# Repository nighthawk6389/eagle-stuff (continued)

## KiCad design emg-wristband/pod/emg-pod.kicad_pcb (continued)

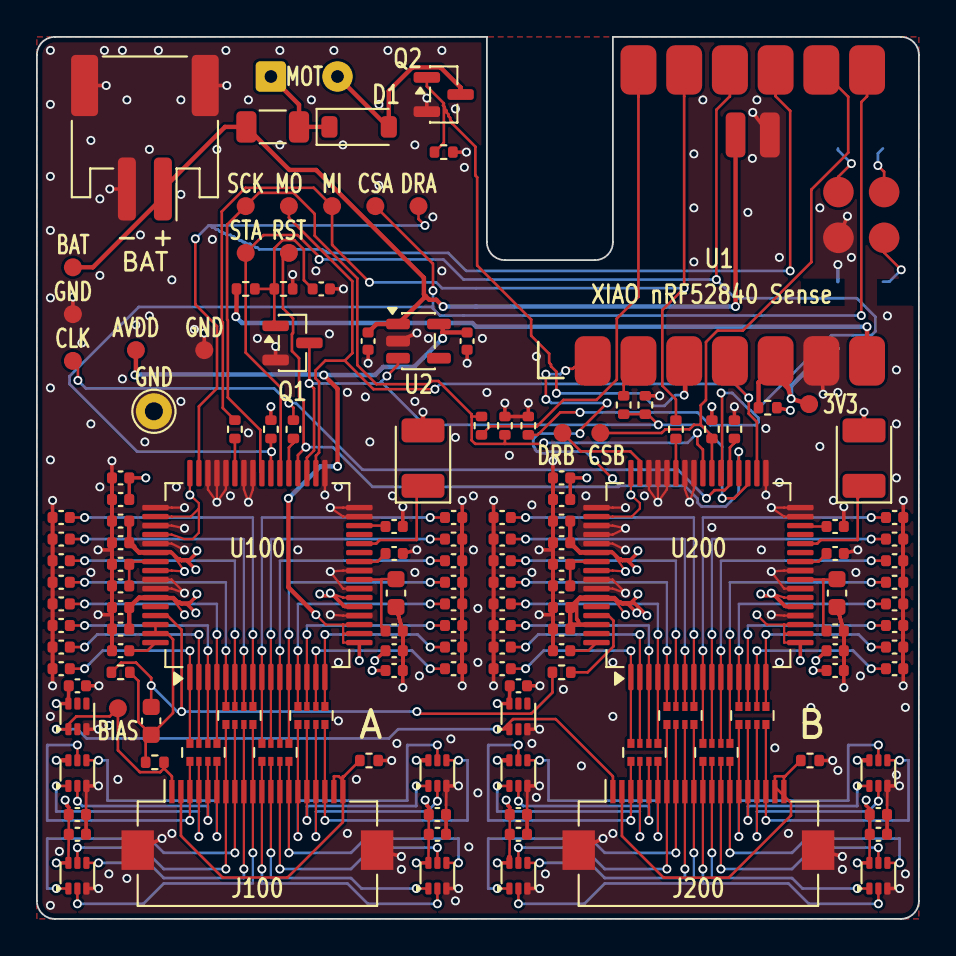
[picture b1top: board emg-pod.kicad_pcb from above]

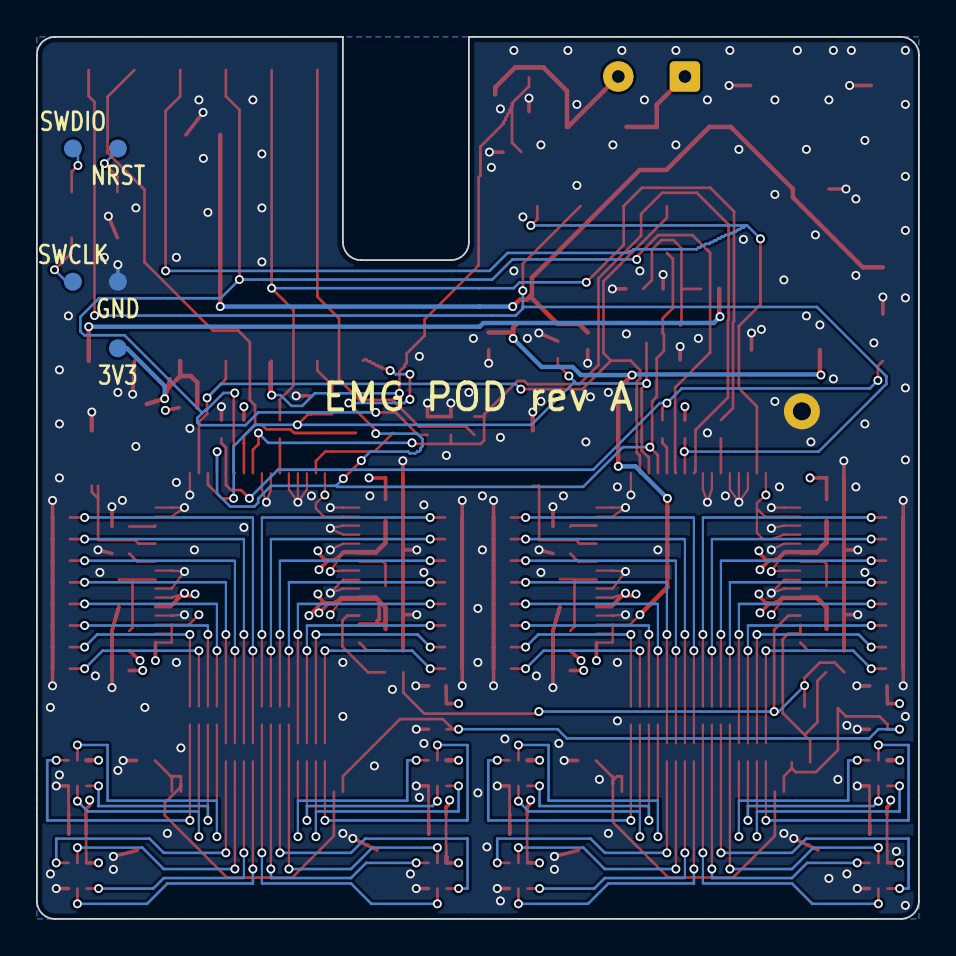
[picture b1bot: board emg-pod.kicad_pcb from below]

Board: 4 copper layers, 49.0 x 49.0 mm, 150 parts (5 on the bottom side), 111 nets.

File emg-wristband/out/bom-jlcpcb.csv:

Comment,Designator,Footprint,LCSC Part #,Manufacturer Part,Quantity
1u,"C1,C2,C120,C122,C124,C126,C131,C132,C134,C220,C222,C224,C226,C231,C232,C234",C_0402_1005Metric,C52923,CL05A105KA5NQNC,16
100n,"C3,C121,C123,C125,C127,C129,C133,C141,C142,C143,C144,C145,C221,C223,C225,C227,C229,C233,C241,C242,C243,C244,C245",C_0402_1005Metric,C1525,CL05B104KO5NNNC,23
47p,"C101,C102,C103,C104,C105,C106,C107,C108,C109,C110,C111,C112,C113,C114,C115,C116,C201,C202,C203,C204,C205,C206,C207,C208,C209,C210,C211,C212,C213,C214,C215,C216",C_0402_1005Metric,C1567,0402CG470J500NT,32
10u,"C128,C228",C_0603_1608Metric,C19702,CL10A106KP8NNNC,2
22u,"C130,C230",CP_EIA-3528-21_Kemet-B,C117031,T491B226M010AT,2
1n,"C135,C235",C_0402_1005Metric,C1523,0402B102K500NT,2
1n5,C140,C_0603_1608Metric,C1595,0603B152K500NT,1
B5819W,D1,D_SOD-123,C8598,B5819W SL,1
S2B-PH-SM4-TB,J1,JST_PH_S2B-PH-SM4-TB_1x02-1MP_P2.00mm_Horizontal,C295747,S2B-PH-SM4-TB(LF)(SN),1
FH12-20S-0.5SH,"J100,J200",Hirose_FH12-20S-0.5SH_1x20-1MP_P0.50mm_Horizontal,C596730,FH12-20S-0.5SH(55),2
AO3400A,"Q1,Q2",SOT-23,C20917,AO3400A,2
10k,"R1,R3,R4,R120,R220",R_0402_1005Metric,C25744,0402WGF1002TCE,5
100k,"R2,R6,R223",R_0402_1005Metric,C25741,0402WGF1003TCE,3
12R,R5,R_0805_2012Metric,C17445,0805W8F120JT5E,1
33R,"R20,R121,R123,R221",R_0402_1005Metric,C25105,0402WGF330JTCE,4
0R,"R122,R222,R224",R_0402_1005Metric,C17168,0402WGF0000TCE,3
1M,R124,R_0402_1005Metric,C26083,0402WGF1004TCE,1
47k,R125,R_0402_1005Metric,C25792,0402WGF4702TCE,1
47k x4,"RN101,RN102,RN103,RN104,RN201,RN202,RN203,RN204",R_Array_Convex_4x0402,C2028,4D02WGJ0473TCE,8
XIAO nRF52840 Sense,U1,XIAO-nRF52840-SMD,C17401557,Seeed 102010469,1
LP5907MFX-3.0,U2,SOT-23-5,C475492,LP5907MFX-3.0/NOPB,1
ADS1298IPAGR,"U100,U200",TQFP-64_10x10mm_P0.5mm,C527440,ADS1298IPAGR,2
TPD4E001DRL,"U101,U102,U103,U104,U105,U201,U202,U203,U204,U205",SOT-563,C527516,TPD4E001DRLR,10

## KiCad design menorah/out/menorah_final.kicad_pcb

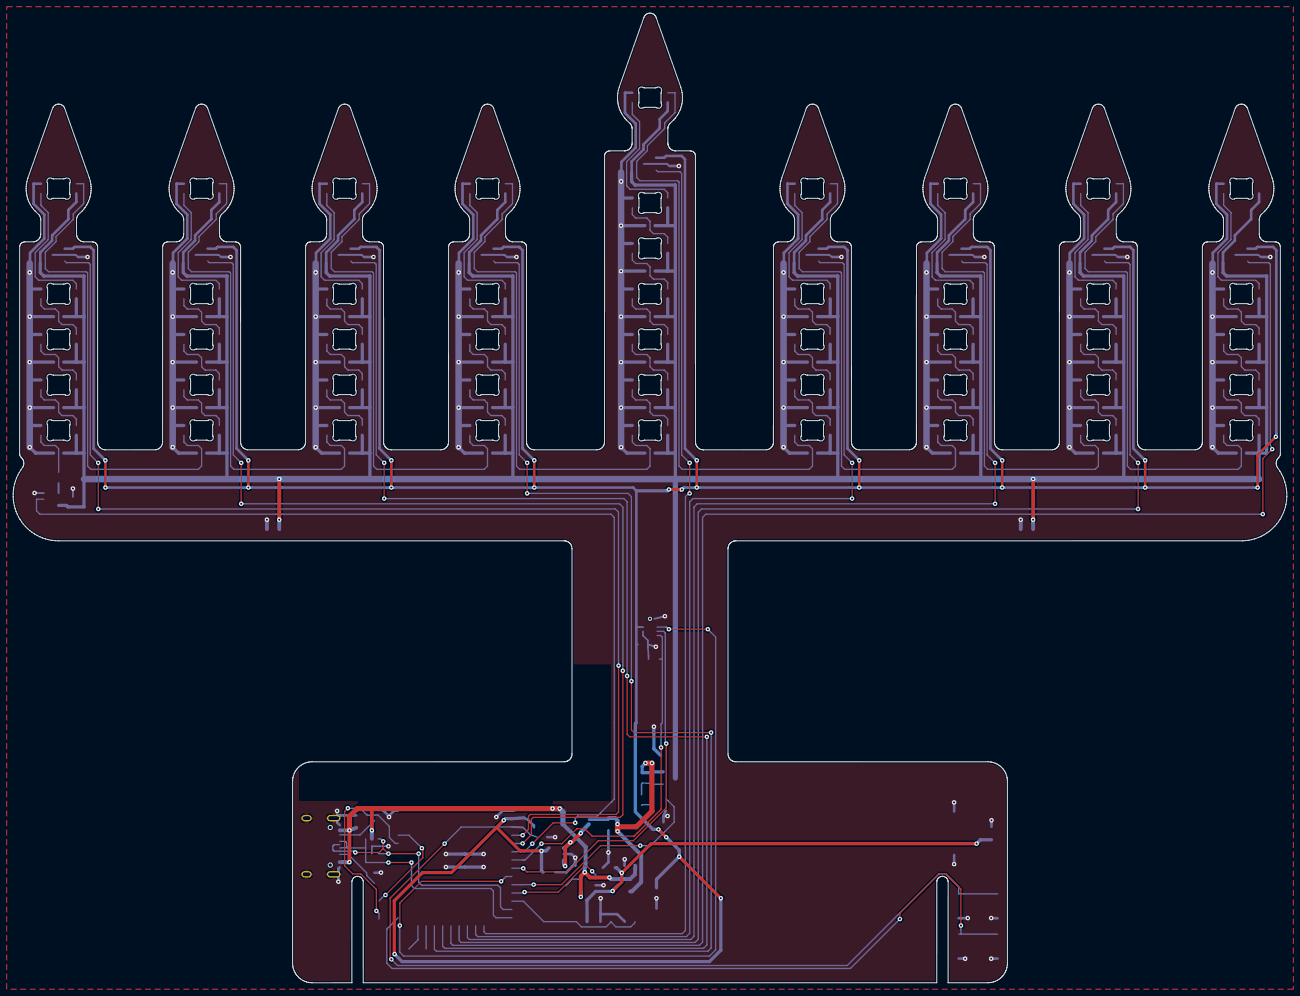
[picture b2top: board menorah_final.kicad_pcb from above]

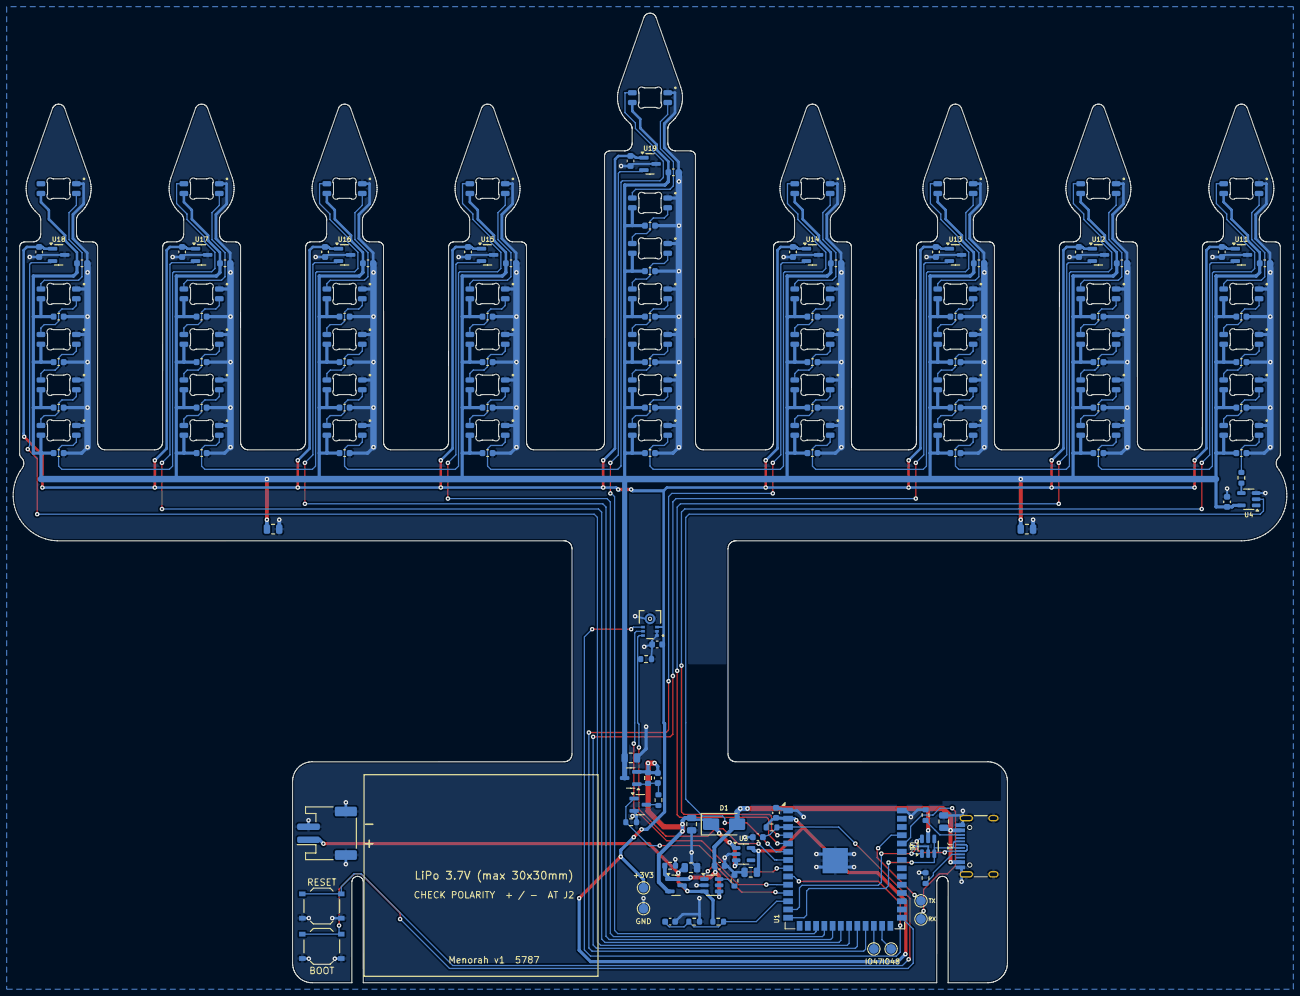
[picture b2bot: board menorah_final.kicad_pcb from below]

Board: 2 copper layers, 196.0 x 149.2 mm, 158 parts (158 on the bottom side), 83 nets.

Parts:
C1, C8, C11, C12, C101, C102, C103, C104, C105, C106, C107, C108, C109, C110, C111, C112, C113, C114, C115, C116, C117, C118, C119, C120, C121, C122, C123, C124, C125, C126, C127, C128, C129, C130, C131, C132, C133, C134, C135, C136, C137, C138, C139, C140, C141, C142, C143, C144, C145, C146, C147, C151, C152, C153, C154, C155, C156, C157, C158, C159: 100n; C_0603_1608Metric
C2, C4, C9: 1u; C_0603_1608Metric
C3, C5: 10u; C_0805_2012Metric
C6, C7, C10, C13, C14: 22u; C_0805_2012Metric
D1: SS34; D_SMA
D101, D102, D103, D104, D105, D106, D107, D108, D109, D110, D111, D112, D113, D114, D115, D116, D117, D118, D119, D120, D121, D122, D123, D124, D125, D126, D127, D128, D129, D130, D131, D132, D133, D134, D135, D136, D137, D138, D139, D140, D141, D142, D143, D144, D145, D146, D147: SK6812MINI-E; SK6812MINI-E_Rev
J1: USB-C; USB_C_Receptacle_HRO_TYPE-C-31-M-12
J2: LiPo; JST_PH_S2B-PH-SM4-TB_1x02-1MP_P2.00mm_Horizontal
MK1: ICS-43432
Q1, Q2: AO3401A; SOT-23
Q3: 2N7002; SOT-23
R1, R9: 10k; R_0603_1608Metric
R2, R3: 5k1; R_0603_1608Metric
R4: 3k3; R_0603_1608Metric
R5: 2k2; R_0603_1608Metric
R6, R7, R8, R10, R12: 100k; R_0603_1608Metric
R11: 100R; R_0603_1608Metric
SW1, SW2: TS-1187A; SW_Push_1P1T_XKB_TS-1187A
TP1: GND; TestPoint_Pad_D1.5mm
TP2: +3V3; TestPoint_Pad_D1.5mm
TP3: TX; TestPoint_Pad_D1.5mm
TP4: RX; TestPoint_Pad_D1.5mm
TP5: IO47; TestPoint_Pad_D1.5mm
TP6: IO48; TestPoint_Pad_D1.5mm
U1: ESP32-S3-WROOM-1-N8R8; ESP32-S3-WROOM-1
U2: TP4057; SOT-23-6
U3: AP2112K-3.3; SOT-23-5
U4: SN74LV1T34; SOT-23-5
U5: USBLC6-2SC6; SOT-23-6
U11, U12, U13, U14, U15, U16, U17, U18, U19: DRV5032FA; SOT-23

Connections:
+3V3: C1.1, C6.1, C12.1, C151.1, C152.1, C153.1, C154.1, C155.1, C156.1, C157.1, C158.1, C159.1, MK1.3, R1.1, TP2.1, U1.2, U3.5, U11.1, U12.1, U13.1, U14.1, U15.1, U16.1, U17.1, U18.1, U19.1
BOOT: SW1.1, U1.27
CC1: J1.A5, R3.1
CC2: J1.B5, R2.1
CHRG_N: U1.11, U2.1
EN: C2.1, R1.2, SW2.1, U1.3
EXP_IO47: TP5.1, U1.24
EXP_IO48: TP6.1, U1.25
GND: C1.2, C2.2, C3.2, C4.2, C5.2, C6.2, C7.2, C8.2, C10.2, C11.2, C12.2, C13.2, C14.2, C101.2, C102.2, C103.2, C104.2, C105.2, C106.2, C107.2, C108.2, C109.2, C110.2, C111.2, C112.2, C113.2, C114.2, C115.2, C116.2, C117.2, C118.2, C119.2, C120.2, C121.2, C122.2, C123.2, C124.2, C125.2, C126.2, C127.2, C128.2, C129.2, C130.2, C131.2, C132.2, C133.2, C134.2, C135.2, C136.2, C137.2, C138.2, C139.2, C140.2, C141.2, C142.2, C143.2, C144.2, C145.2, C146.2, C147.2, C151.2, C152.2, C153.2, C154.2, C155.2, C156.2, C157.2, C158.2, C159.2, D101.3, D102.3, D103.3, D104.3, D105.3, D106.3, D107.3, D108.3, D109.3, D110.3, D111.3, D112.3, D113.3, D114.3, D115.3, D116.3, D117.3, D118.3, D119.3, D120.3, D121.3, D122.3, D123.3, D124.3, D125.3, D126.3, D127.3, D128.3, D129.3, D130.3, D131.3, D132.3, D133.3, D134.3, D135.3, D136.3, D137.3, D138.3, D139.3, D140.3, D141.3, D142.3, D143.3, D144.3, D145.3, D146.3, D147.3, J1.A1, J1.A12, J1.B1, J1.B12, J1.S1, J2.2, J2.MP, MK1.1, MK1.2, MK1.4, Q3.2, R2.2, R3.2, R4.2, R5.2, R7.2, R10.2, R12.2, SW1.2, SW2.2, TP1.1, U1.1, U1.40, U1.41, U2.2, U3.2, U4.3, U5.2, U11.3, U12.3, U13.3, U14.3, U15.3, U16.3, U17.3, U18.3, U19.3
HALL_C1: U1.4, U11.2
HALL_C2: U1.5, U12.2
HALL_C3: U1.22, U13.2
HALL_C4: U1.23, U14.2
HALL_C5: U1.18, U15.2
HALL_C6: U1.19, U16.2
HALL_C7: U1.20, U17.2
HALL_C8: U1.21, U18.2
HALL_SH: U1.17, U19.2
LED_D0: D101.4, R11.2
LED_D1: D101.2, D102.4
LED_D2: D102.2, D103.4
LED_D3: D103.2, D104.4
LED_D4: D104.2, D105.4
LED_D5: D105.2, D106.4
LED_D6: D106.2, D107.4
LED_D7: D107.2, D108.4
LED_D8: D108.2, D109.4
LED_D9: D109.2, D110.4
LED_D10: D110.2, D111.4
LED_D11: D111.2, D112.4
LED_D12: D112.2, D113.4
LED_D13: D113.2, D114.4
LED_D14: D114.2, D115.4
LED_D15: D115.2, D116.4
LED_D16: D116.2, D117.4
LED_D17: D117.2, D118.4
LED_D18: D118.2, D119.4
LED_D19: D119.2, D120.4
LED_D20: D120.2, D121.4
LED_D21: D121.2, D122.4
LED_D22: D122.2, D123.4
LED_D23: D123.2, D124.4
LED_D24: D124.2, D125.4
LED_D25: D125.2, D126.4
LED_D26: D126.2, D127.4
LED_D27: D127.2, D128.4
LED_D28: D128.2, D129.4
LED_D29: D129.2, D130.4
LED_D30: D130.2, D131.4
LED_D31: D131.2, D132.4
LED_D32: D132.2, D133.4
LED_D33: D133.2, D134.4
LED_D34: D134.2, D135.4
LED_D35: D135.2, D136.4
LED_D36: D136.2, D137.4
LED_D37: D137.2, D138.4
LED_D38: D138.2, D139.4
LED_D39: D139.2, D140.4
LED_D40: D140.2, D141.4
LED_D41: D141.2, D142.4
LED_D42: D142.2, D143.4
LED_D43: D143.2, D144.4
LED_D44: D144.2, D145.4
LED_D45: D145.2, D146.4
LED_D46: D146.2, D147.4
LED_DATA_3V3: U1.6, U4.2
LED_DATA_5V: R11.1, U4.4
MIC_SCK: MK1.6, U1.8
MIC_SD: MK1.7, R12.1, U1.7
MIC_WS: MK1.5, U1.9
PROG: R4.1, U2.6
Q2_G: C9.2, Q2.1, R8.2, R9.1
Q3_D: Q3.3, R9.2
UART_RX: TP4.1, U1.36
UART_TX: TP3.1, U1.37
USB_DN: J1.A7, J1.B7, U1.13, U5.1, U5.6
USB_DP: J1.A6, J1.B6, U1.14, U5.3, U5.4
VBAT: C5.1, J2.1, Q1.3, R6.1, U2.3
VBAT_SENSE: C8.1, R6.2, R7.1, U1.12
VBUS: C3.1, C4.1, D1.2, J1.A4, J1.A9, J1.B4, J1.B9, Q1.1, R5.1, U2.4, U5.5
VLED: C10.1, C11.1, C13.1, C14.1, C101.1, C102.1, C103.1, C104.1, C105.1, C106.1, C107.1, C108.1, C109.1, C110.1, C111.1, C112.1, C113.1, C114.1, C115.1, C116.1, C117.1, C118.1, C119.1, C120.1, C121.1, C122.1, C123.1, C124.1, C125.1, C126.1, C127.1, C128.1, C129.1, C130.1, C131.1, C132.1, C133.1, C134.1, C135.1, C136.1, C137.1, C138.1, C139.1, C140.1, C141.1, C142.1, C143.1, C144.1, C145.1, C146.1, C147.1, D101.1, D102.1, D103.1, D104.1, D105.1, D106.1, D107.1, D108.1, D109.1, D110.1, D111.1, D112.1, D113.1, D114.1, D115.1, D116.1, D117.1, D118.1, D119.1, D120.1, D121.1, D122.1, D123.1, D124.1, D125.1, D126.1, D127.1, D128.1, D129.1, D130.1, D131.1, D132.1, D133.1, D134.1, D135.1, D136.1, D137.1, D138.1, D139.1, D140.1, D141.1, D142.1, D143.1, D144.1, D145.1, D146.1, D147.1, Q2.3, U4.5
VLED_EN: Q3.1, R10.1, U1.10
VSYS: C7.1, C9.1, D1.1, Q1.2, Q2.2, R8.1, U3.1, U3.3

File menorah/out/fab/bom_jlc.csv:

Comment,Designator,Footprint,LCSC Part #
ESP32-S3-WROOM-1-N8R8,U1,ESP32-S3-WROOM-1,C2913201
100n,"C1,C8,C11,C12,C101,C102,C103,C104,C105,C106,C107,C108,C109,C110,C111,C112,C113,C114,C115,C116,C117,C118,C119,C120,C121,C122,C123,C124,C125,C126,C127,C128,C129,C130,C131,C132,C133,C134,C135,C136,C137,C138,C139,C140,C141,C142,C143,C144,C145,C146,C147,C151,C152,C153,C154,C155,C156,C157,C158,C159",C_0603_1608Metric,C14663
10k,"R1,R9",R_0603_1608Metric,C25804
1u,"C2,C4,C9",C_0603_1608Metric,C15849
TS-1187A,"SW1,SW2",SW_Push_1P1T_XKB_TS-1187A,C318884
USB-C,J1,USB_C_Receptacle_HRO_TYPE-C-31-M-12,C165948
5k1,"R2,R3",R_0603_1608Metric,C23186
USBLC6-2SC6,U5,SOT-23-6,C7519
10u,"C3,C5",C_0805_2012Metric,C15850
SS34,D1,D_SMA,C8678
TP4057,U2,SOT-23-6,C12044
3k3,R4,R_0603_1608Metric,C22978
AO3401A,"Q1,Q2",SOT-23,C15127
2k2,R5,R_0603_1608Metric,C4190
LiPo,J2,JST_PH_S2B-PH-SM4-TB_1x02-1MP_P2.00mm_Horizontal,C295747
AP2112K-3.3,U3,SOT-23-5,C51118
22u,"C6,C7,C10,C13,C14",C_0805_2012Metric,C45783
100k,"R6,R7,R8,R10,R12",R_0603_1608Metric,C25803
2N7002,Q3,SOT-23,C8545
SN74LV1T34,U4,SOT-23-5,C100024
100R,R11,R_0603_1608Metric,C22775
ICS-43432,MK1,ICS-43432,C574021
SK6812MINI-E,"D101,D102,D103,D104,D105,D106,D107,D108,D109,D110,D111,D112,D113,D114,D115,D116,D117,D118,D119,D120,D121,D122,D123,D124,D125,D126,D127,D128,D129,D130,D131,D132,D133,D134,D135,D136,D137,D138,D139,D140,D141,D142,D143,D144,D145,D146,D147",SK6812MINI-E_Rev,C5149201
DRV5032FA,"U11,U12,U13,U14,U15,U16,U17,U18,U19",SOT-23,C140921

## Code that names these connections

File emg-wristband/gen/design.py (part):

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
    # interlock
    s.text("USB interlock: analog rail off whenever VBUS is present", (25.4, 86.5), 1.8, bold=True)
    s.glabel("AFE_EN", (33.02, 99.06), "input", 180)
    r1 = d.add("R1K", "R1", 41.91, 99.06, 90, {1: "AFE_EN", 2: "AVDD_EN"})
    s.wire((33.02, 99.06), r1.p(1))
    s.wire(r1.p(2), (76.2, 99.06))
    s.wire((76.2, 99.06), (83.82, 99.06))
    s.glabel("AVDD_EN", (83.82, 99.06), "output", 0)
    r2 = d.add("R10K", "R2", 55.88, 102.87, 0, {1: "AVDD_EN", 2: "GND"})
    s.power("GND", r2.p(2))
    q1 = d.add("NFET", "Q1", 73.66, 109.22, 0, {1: "VBUS_DET", 2: "GND", 3: "AVDD_EN"},
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    r3 = d.add("R10K", "R3", 41.91, 121.92, 90, {1: "VBUS", 2: "VBUS_DET"})
    s.wire((33.02, 121.92), r3.p(1))
    s.wire(r3.p(2), (66.04, 121.92), (66.04, 109.22), q1.p(1))
    s.label("VBUS_DET", (46.99, 121.92))
    r4 = d.add("R10K", "R4", 50.8, 125.73, 0, {1: "VBUS_DET", 2: "GND"})
    s.power("GND", r4.p(2))
    c3 = d.add("C100N", "C3", 59.69, 125.73, 0, {1: "VBUS_DET", 2: "GND"})
    s.power("GND", c3.p(2))
    s.text("VBUS is the XIAO 5V pin, which Seeed wires straight to the USB connector.\n"
           "With USB present Q1 shorts AVDD_EN to ground; R1 keeps the MCU pin from\n"
           "overriding it, so firmware cannot turn the analog rail on.\n"
           "Trip point: Q1 turns on for VBUS between 1.3 V and 2.9 V\n"
           "(Vgs(th) 0.65 to 1.45 V, AO3400A datasheet; R3/R4 halve VBUS).\n"
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    d1 = d.add("SCHOTTKY", "D1", 152.4, 110.49, 270, {1: "MOT_P", 2: "MOT_N"})
    s.wire(r5.p(2), d1.p(1))
    s.wire((152.4, 101.6), (165.1, 101.6), (165.1, 104.14), (170.18, 104.14))
    s.label("MOT_P", (154.94, 101.6))
    j2 = s.place("Connector_Generic:Conn_01x02", "J2", "Motor pads", 175.26, 104.14, 0, footprint=FP_MOTOR,
                 in_bom=False, ref_at=(176.53, 99.9, ""), val_at=(179.5, 105.41, "left"))
    d.nets(j2, {1: "MOT_P", 2: "MOT_N"})
    s.wire(j2.p(2), (165.1, 106.68), (165.1, 116.84), (152.4, 116.84))
    s.label("MOT_N", (154.94, 116.84))
    q2 = d.add("NFET", "Q2", 149.86, 127.0, 0, {1: "MOTOR", 2: "GND", 3: "MOT_N"},
               ref_at=(154.94, 125.73, "left"), val_at=(154.94, 128.27, "left"))
    s.wire(d1.p(2), q2.p(3))
    d.stub(q2, 2, 2.54)
    s.glabel("MOTOR", (127.0, 127.0), "input", 180)
    s.wire((127.0, 127.0), q2.p(1))
    r6 = d.add("R100K", "R6", 137.16, 130.81, 0, {1: "MOTOR", 2: "GND"})
    s.power("GND", r6.p(2))
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    for pin in range(1, 21):
        d.stub(j, pin, 5.08)
    d.stub(j, "MP", 2.54)
    s.text("Strip tail connector, 20 way 0.5 mm.\nPin 1 bias, pins 3-18 the eight pairs\n(channel 8 first), pins 2, 19, 20 shield.",
           (66.5, 62.0), 1.1, justify="left top")

    # ---- ESD arrays at the connector
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        d.stub(u, 62, 5.08)
        d.stub(u, 61, 5.08)
    d.stub(u, 60, 0)
    s.text("Strapped per the datasheet: TESTP/TESTN (unused inputs) to AVDD; DAISY_IN, GPIO1-4 and RESV1 to DGND;\n"
           "pins 27 and 29 are not connected. Firmware must leave GPIO1-4 as inputs, their reset state.",
           (140.0, 236.0), 1.1, justify="left top")

    # ---- input network: series resistor in each line, capacitor at the converter pin
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    # ---- bypass
    s.text("Supply bypass (1 uF + 100 nF at each supply group)", (246.38, 93.0), 1.5, bold=True)
    c = b + 20
    sup = [("AVDD", [("C1U", f"C{c}"), ("C100N", f"C{c + 1}")], "AVDD pins\n19, 21, 22"),
           ("AVDD", [("C1U", f"C{c + 2}"), ("C100N", f"C{c + 3}")], "AVDD pins\n56, 59"),
           ("AVDD", [("C1U", f"C{c + 4}"), ("C100N", f"C{c + 5}")], "AVDD1\npin 54"),
           ("DVDD", [("C1U", f"C{c + 6}"), ("C100N", f"C{c + 7}")], "DVDD pins\n48, 50")]
    d.bank(248.92, 109.22, sup, 12.7)
    s.text("Reference and internal nodes", (246.38, 128.5), 1.5, bold=True)
    ref = [(P + "VREFP", [("C10U", f"C{c + 8}"), ("C100N", f"C{c + 9}")], "VREFP to\nVREFN"),
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    y1, y2, y3 = 190.5, 210.82, 231.14
    s.text("Straps and series parts", (246.38, 179.0), 1.5, bold=True)
    d.two("R100K", f"R{b + 20}", 254.0, y1, "H", "DVDD", "CS_" + X, 5.08)
    s.text("chip select pull-up (the MCU pin floats in reset).\nPWDN is on AVDD_EN: the converter is powered\n"
           "down whenever the analog rail is off", (243.84, y1 + 3.3), 1.0, justify="left top")
    d.two("R33", f"R{b + 21}", 299.72, y1, "H", P + "DOUT", "MISO", 5.08)
    s.text("series resistor at the data output", (287.0, y1 + 5.0), 1.0, justify="left top")
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        cc = d.add("C1N5", f"C{b + 40}", 266.7, y3 + 10.16, 90, {1: "A_RLDOUT", 2: "RLDINV"})
        s.wire(r.p(1), (257.81, y3))
        s.wire(cc.p(1), (260.35, y3 + 10.16), (260.35, y3))
        s.label("A_RLDOUT", (257.81, y3), 180)
        s.wire(r.p(2), (275.59, y3))
        s.wire(cc.p(2), (273.05, y3 + 10.16), (273.05, y3))
        s.glabel("RLDINV", (275.59, y3), "passive", 0)
        s.text("feedback 1 Mohm and 1.5 nF, the typical\nvalues of SBAS459K figures 33, 43, 94",
               (257.0, y3 + 16.5), 1.0, justify="left top")
        d.two("RSKIN", f"R{b + 25}", 325.12, y3, "H", "A_RLDOUT", "BIAS", 5.08)
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        s.text("keeps the clock input low until converter A drives it", (254.0, y2 + 3.0), 1.0, justify="left top")
        s.text("Bias amplifier of converter B is not used (left powered down)", (246.38, y3 - 12.5), 1.5, bold=True)
        d.two("R0", f"R{b + 24}", 266.7, y3, "H", "B_RLDINV", "RLDINV", 5.08)
        s.text("joins the two RLDINV pins as in SBAS459K figure 45,\nso converter B's channels can feed the bias loop.\n"
               "RLDIN goes to AVDD (unused pin, footnote 1 of the pin table);\nRLDOUT and RLDREF stay open.",
               (254.0, y3 + 5.0), 1.0, justify="left top")


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
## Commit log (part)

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2018-08-03 Initial
